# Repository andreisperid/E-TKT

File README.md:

<br>

<a href="https://certification.oshwa.org/br000010.html" target="_blank">
  <picture>
    <source media="(prefers-color-scheme: dark)" srcset="https://user-images.githubusercontent.com/15098003/196943625-ccef0886-9a68-493c-814a-6e63b238b2bd.png">
    <source media="(prefers-color-scheme: light)" srcset="https://user-images.githubusercontent.com/15098003/196943559-973e30a0-acfd-4a96-a7b8-da4f9bf773d8.png">
    
  </picture>
</a>

<br>

<h1 align="center">E-TKT: anachronic label maker</h1>
<h5 align="center">Andrei Speridião - 2022 - <a href="https://andrei.cc">andrei.cc</a></h6>

<br>

<h3 align="center"><i>An open source label maker that fuses together both old and contemporary technology to create something as ubiquitous as... EMBOSSED LABELS!</i></h2>

<br>

By combining simple and widely available embossing tapes in a reliable mechanism with modern connectivity, E-TKT rescues a *would-be future* that did not happen, and at the same time *gets rid of the dependence on proprietary cartridges*, which are environmentally impacting & expensive.

<br>
<br>

<br>

<br><br>

# how does it work?

<picture>
  <source media="(prefers-color-scheme: dark)" srcset="https://user-images.githubusercontent.com/15098003/196457261-b6343e3f-528d-4cbe-a548-1b4f4463e4a1.png">
  <source media="(prefers-color-scheme: light)" srcset="https://user-images.githubusercontent.com/15098003/196947337-6aefe414-159e-483b-9dc4-a49cfc82c548.png">
  
</picture>

An *ESP32* commands the label production and also serves an on demand web application (local) to any device connected in a local network.

***Neither internet is needed, nor installing any app.***

<br>

# documentation 

It's now much more detailed, so I've moved it to a [dedicated page](https://andreisperid.github.io/E-TKT/).

### What you fill find there:

- [🎯 news](https://andreisperid.github.io/E-TKT/news.html): what's going on;
- [🤓 about](https://andreisperid.github.io/E-TKT/about.html): how it started, and why?
- [⚙️ how does it work?](https://andreisperid.github.io/E-TKT/how.html): a more in depth explanation;
- [💡 features](https://andreisperid.github.io/E-TKT/features.html): device and app details;
- [📷 gallery](https://andreisperid.github.io/E-TKT/gallery.html): misc. photos of the device and labeled things;
- [🛠️ do it yourself](https://andreisperid.github.io/E-TKT/diy/diy.html): a **super** detailed guide for you to buy the parts and make your own E-TKT;
- [🧬 iterations](https://andreisperid.github.io/E-TKT/iterations/iterations.html): a log of development so far;
- [⚖️ license](https://andreisperid.github.io/E-TKT/license.html): for firmware, hardware and documentation itself;
- [🏅 credits](https://andreisperid.github.io/E-TKT/credits/credits.html): people that made a difference for the project;
- [📺 media](https://andreisperid.github.io/E-TKT/media.html): where and when it's already been featured.

<br>

### If you ever build one, [I would love to know](mailto:hi@andrei.cc) ;)

### And if you'd like, [donations](https://www.paypal.com/donate/?business=U5QYSBT2TLZL8&no_recurring=0&currency_code=USD) are more than welcome 😍

<br>

### *...for other projects: [andrei.cc](https://andrei.cc)*

<br>

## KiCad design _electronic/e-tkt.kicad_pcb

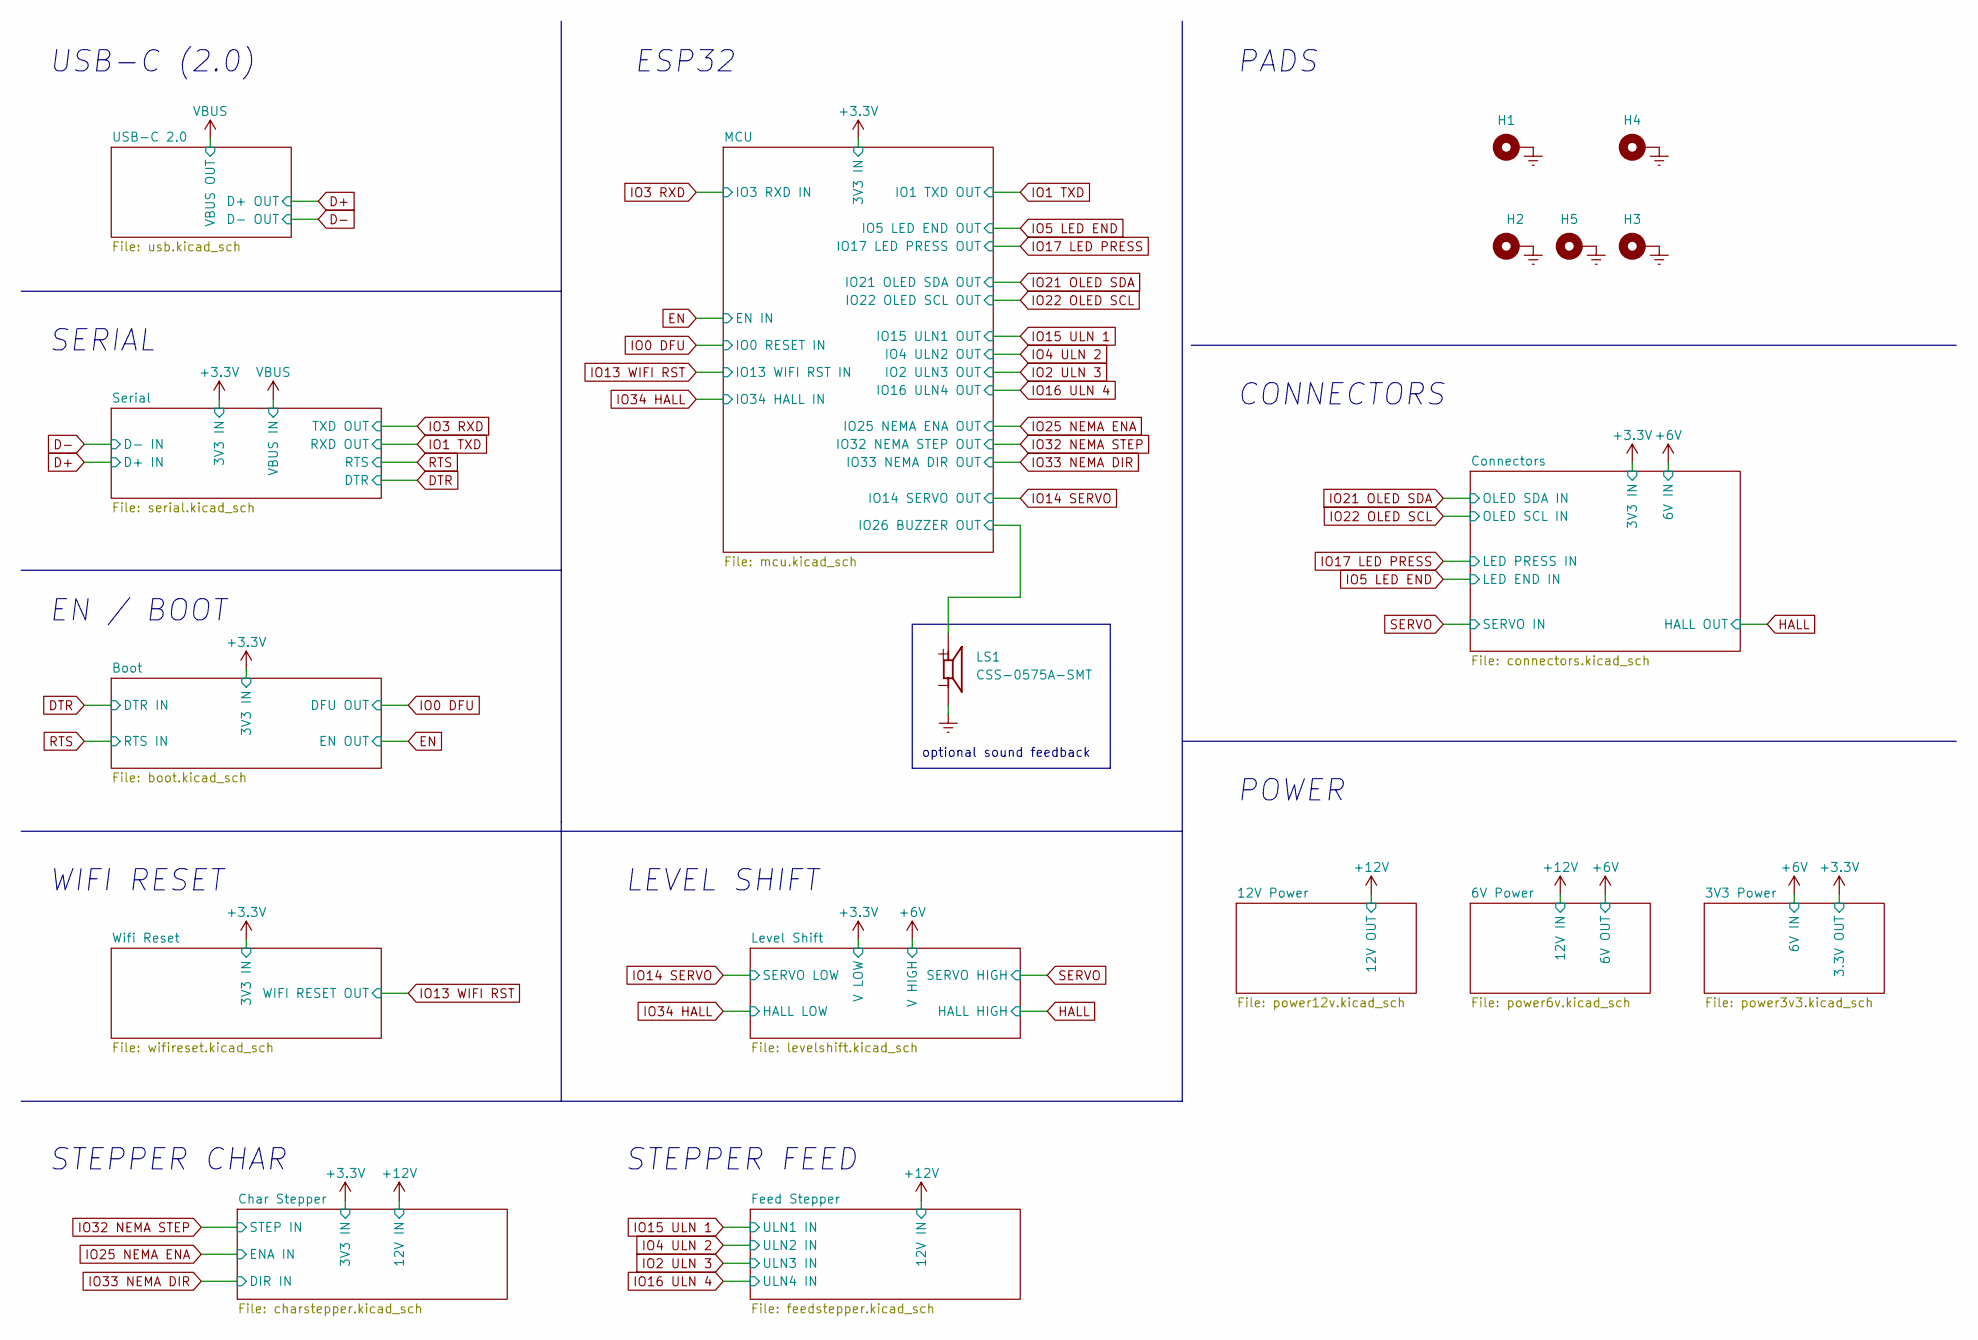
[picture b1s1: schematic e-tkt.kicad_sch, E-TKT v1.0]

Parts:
H1, H2, H3, H4, H5: M3; MountingHole_3.2mm_M3_Pad_Via; Mouser OK
LS1: CSS-0575A-SMT; CUI_CSS-0575A-SMT; Mouser OK

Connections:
/MCU/IO26 BUZZER OUT: LS1.1; also elsewhere on the board

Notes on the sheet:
PADS
POWER
optional sound feedback
SERIAL
EN / BOOT
CONNECTORS
STEPPER CHAR
WIFI RESET
ESP32
LEVEL SHIFT
STEPPER FEED
USB-C (2.0)

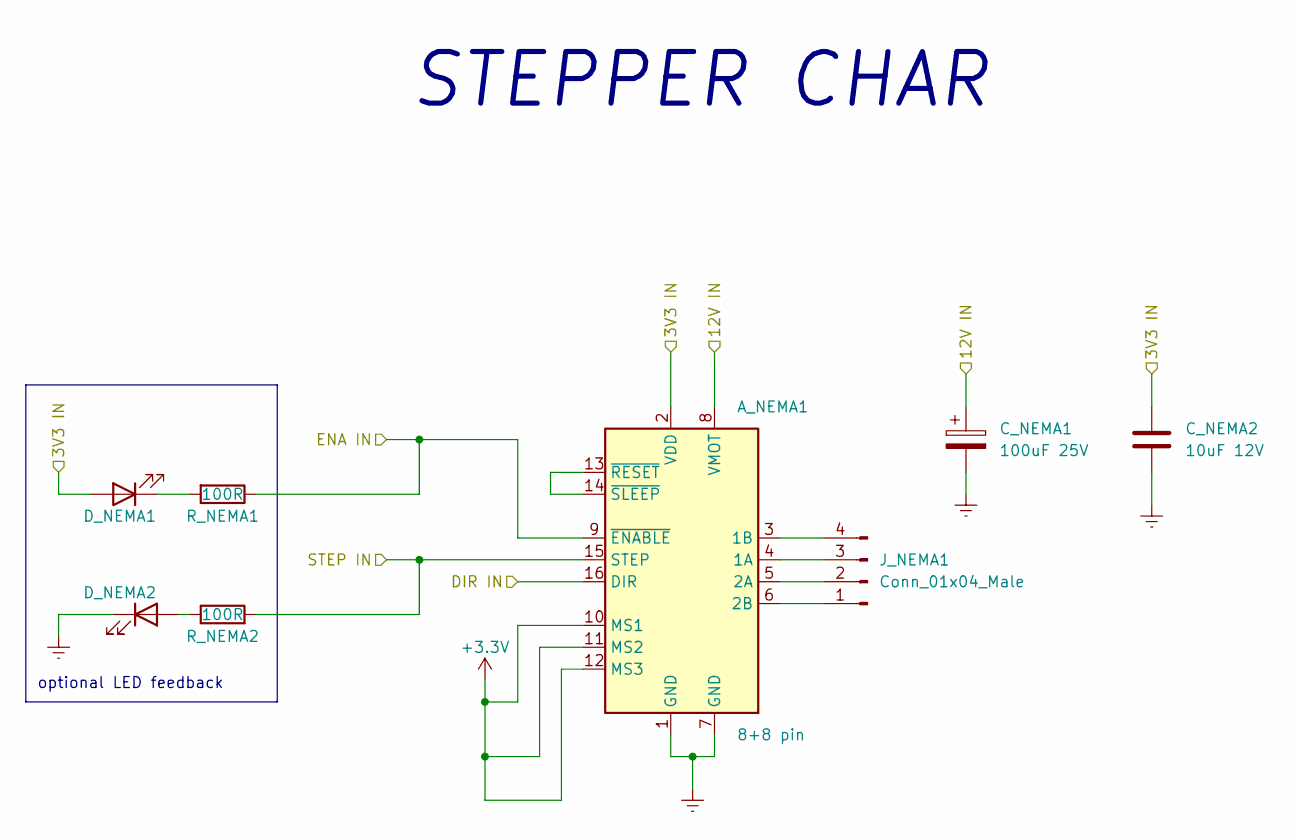
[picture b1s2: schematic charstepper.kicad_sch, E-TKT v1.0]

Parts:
A_NEMA1: 8+8 pin; Pololu_Breakout-16_15.2x20.3mm; Mouser OK
C_NEMA1: 100uF 25V; CP_Elec_6.3x7.7; Mouser OK
C_NEMA2: 10uF 12V; C_0603_1608Metric_Pad1.08x0.95mm_HandSolder; Mouser OK
D_NEMA1, D_NEMA2: LED white; LED_0603_1608Metric_Pad1.05x0.95mm_HandSolder; Mouser OK
J_NEMA1: Conn_01x04_Male; PinHeader_1x04_P2.54mm_Horizontal; Mouser OK
R_NEMA1, R_NEMA2: 100R; R_0603_1608Metric_Pad0.98x0.95mm_HandSolder; Mouser OK

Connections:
+3.3V: A_NEMA1.2 (VDD), A_NEMA1.10 (MS1), A_NEMA1.11 (MS2), A_NEMA1.12 (MS3), C_NEMA2.2, D_NEMA1.2 (A); also elsewhere on the board
+12V: A_NEMA1.8 (VMOT), C_NEMA1.1; also elsewhere on the board
IO25 NEMA ENA: A_NEMA1.9 (~ENABLE), R_NEMA1.1; also elsewhere on the board
IO32 NEMA STEP: A_NEMA1.15 (STEP), R_NEMA2.2; also elsewhere on the board
IO33 NEMA DIR: A_NEMA1.16 (DIR); also elsewhere on the board
unnamed: A_NEMA1.3 (1B), J_NEMA1.4
unnamed: A_NEMA1.4 (1A), J_NEMA1.3
unnamed: A_NEMA1.5 (2A), J_NEMA1.2
unnamed: A_NEMA1.6 (2B), J_NEMA1.1
unnamed: A_NEMA1.13 (~RESET), A_NEMA1.14 (~SLEEP)
unnamed: D_NEMA1.1 (K), R_NEMA1.2
unnamed: D_NEMA2.2 (A), R_NEMA2.1

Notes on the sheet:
optional LED feedback
STEPPER CHAR

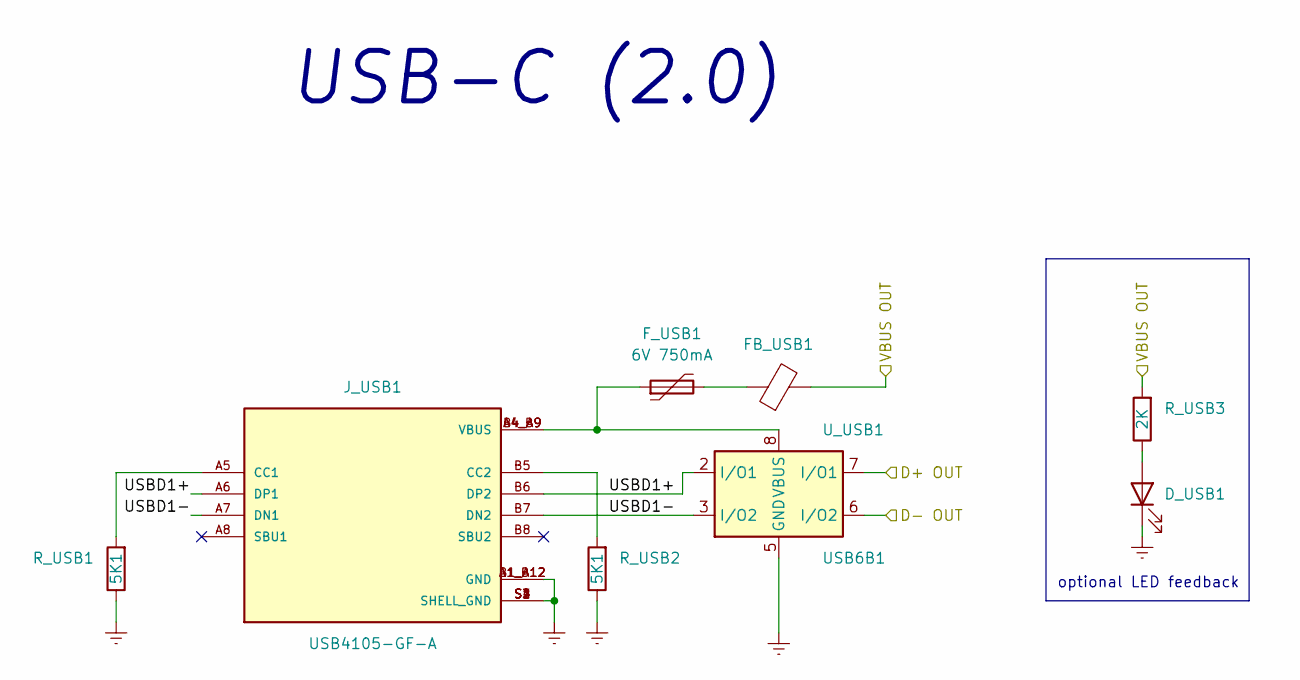
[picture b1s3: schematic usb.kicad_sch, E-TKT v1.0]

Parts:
D_USB1: LED white; LED_0603_1608Metric_Pad1.05x0.95mm_HandSolder; Mouser OK
FB_USB1: 40 Ohms @ 100 MHz 1 Power; L_0805_2012Metric_Pad1.05x1.20mm_HandSolder; Mouser OK
F_USB1: 6V 750mA; Fuse_0805_2012Metric_Pad1.15x1.40mm_HandSolder; Mouser OK
J_USB1: USB4105-GF-A; GCT_USB4105-GF-A; Mouser OK
R_USB1, R_USB2: 5K1; R_0603_1608Metric_Pad0.98x0.95mm_HandSolder; Mouser OK
R_USB3: 2K; R_0603_1608Metric_Pad0.98x0.95mm_HandSolder; Mouser OK
U_USB1: USB6B1; SOIC-8_3.9x4.9mm_P1.27mm; Mouser OK

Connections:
/USB-C 2.0/USBD1+: J_USB1.A6 (DP1), J_USB1.B6 (DP2), U_USB1.2 (I/O1)
/USB-C 2.0/USBD1-: J_USB1.A7 (DN1), J_USB1.B7 (DN2), U_USB1.3 (I/O2)
D+: U_USB1.7 (I/O1); also elsewhere on the board
D-: U_USB1.6 (I/O2); also elsewhere on the board
unnamed: D_USB1.2 (A), R_USB3.1
unnamed: FB_USB1.1, F_USB1.2
unnamed: F_USB1.1, J_USB1.A4_B9 (VBUS), J_USB1.B4_A9 (VBUS), U_USB1.1 (VBUS), U_USB1.8 (VBUS)
unnamed: J_USB1.A5 (CC1), R_USB1.2
unnamed: J_USB1.B5 (CC2), R_USB2.2
VBUS: FB_USB1.2, R_USB3.2; also elsewhere on the board

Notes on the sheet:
USB-C (2.0)
optional LED feedback

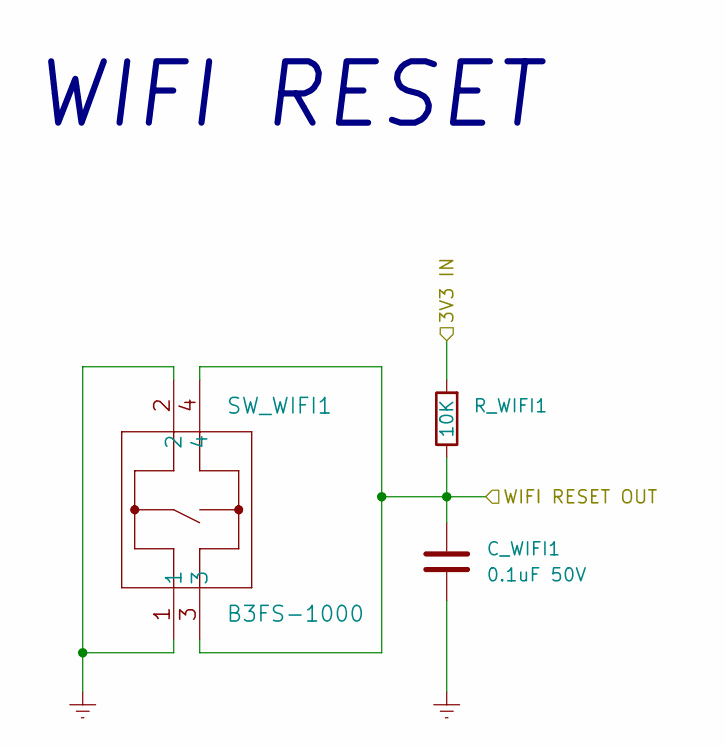
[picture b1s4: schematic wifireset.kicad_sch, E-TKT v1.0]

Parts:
C_WIFI1: 0.1uF 50V; C_0603_1608Metric_Pad1.08x0.95mm_HandSolder; Mouser OK
R_WIFI1: 10K; R_0603_1608Metric_Pad0.98x0.95mm_HandSolder; Mouser OK
SW_WIFI1: B3FS-1000; Mouser OK

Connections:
+3.3V: R_WIFI1.2; also elsewhere on the board
IO13 WIFI RST: C_WIFI1.2, R_WIFI1.1, SW_WIFI1.3, SW_WIFI1.4; also elsewhere on the board

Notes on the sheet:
WIFI RESET

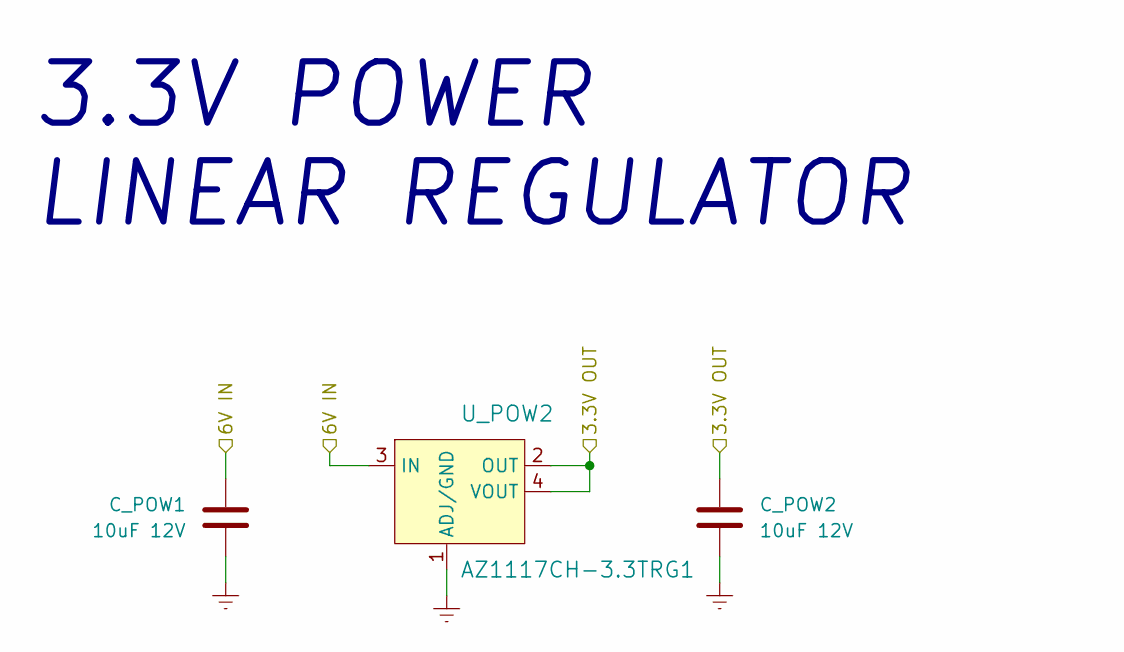
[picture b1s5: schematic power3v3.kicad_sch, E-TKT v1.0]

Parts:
C_POW1, C_POW2: 10uF 12V; C_0603_1608Metric_Pad1.08x0.95mm_HandSolder; Mouser OK
U_POW2: AZ1117CH-3.3TRG1; SOT-223; Mouser OK

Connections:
+3.3V: C_POW2.1, U_POW2.2 (OUT), U_POW2.4 (VOUT); also elsewhere on the board
+6V: C_POW1.1, U_POW2.3 (IN); also elsewhere on the board

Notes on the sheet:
3.3V POWER LINEAR REGULATOR

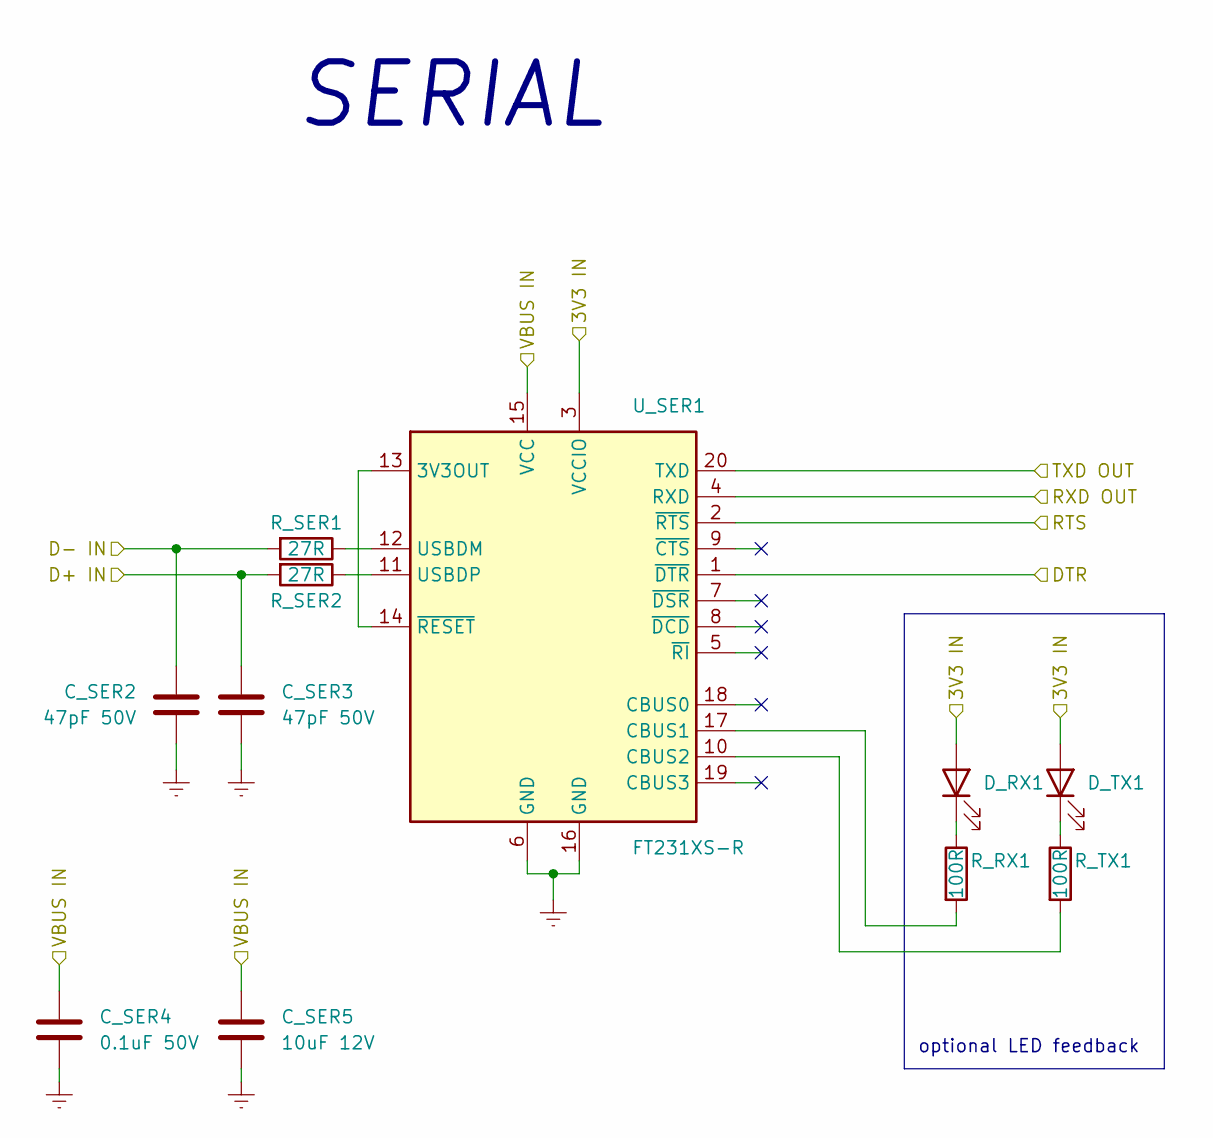
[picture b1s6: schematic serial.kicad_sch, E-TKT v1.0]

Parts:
C_SER2, C_SER3: 47pF 50V; C_0603_1608Metric_Pad1.08x0.95mm_HandSolder; Mouser OK
C_SER4: 0.1uF 50V; C_0603_1608Metric_Pad1.08x0.95mm_HandSolder; Mouser OK
C_SER5: 10uF 12V; C_0603_1608Metric_Pad1.08x0.95mm_HandSolder; Mouser OK
D_RX1: LED white; LED_0603_1608Metric_Pad1.05x0.95mm_HandSolder; Mouser OK
D_TX1: LED white; LED_0603_1608Metric_Pad1.05x0.95mm_HandSolder; Mouser OK
R_RX1: 100R; R_0603_1608Metric_Pad0.98x0.95mm_HandSolder; Mouser OK
R_SER1, R_SER2: 27R; R_0603_1608Metric_Pad0.98x0.95mm_HandSolder; Mouser OK
R_TX1: 100R; R_0603_1608Metric_Pad0.98x0.95mm_HandSolder; Mouser OK
U_SER1: FT231XS-R; SSOP-20_3.9x8.7mm_P0.635mm; Mouser OK

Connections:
+3.3V: D_RX1.2 (A), D_TX1.2 (A), U_SER1.3 (VCCIO); also elsewhere on the board
D+: C_SER3.2, R_SER2.2; also elsewhere on the board
D-: C_SER2.2, R_SER1.2; also elsewhere on the board
DTR: U_SER1.1 (~DTR); also elsewhere on the board
IO1 TXD: U_SER1.4 (RXD); also elsewhere on the board
IO3 RXD: U_SER1.20 (TXD); also elsewhere on the board
unnamed: D_RX1.1 (K), R_RX1.1
unnamed: D_TX1.1 (K), R_TX1.1
unnamed: R_RX1.2, U_SER1.17 (CBUS1)
unnamed: R_SER1.1, U_SER1.12 (USBDM)
unnamed: R_SER2.1, U_SER1.11 (USBDP)
unnamed: R_TX1.2, U_SER1.10 (CBUS2)
unnamed: U_SER1.13 (3V3OUT), U_SER1.14 (~RESET)
RTS: U_SER1.2 (~RTS); also elsewhere on the board
VBUS: C_SER4.1, C_SER5.2, U_SER1.15 (VCC); also elsewhere on the board

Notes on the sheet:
SERIAL
optional LED feedback

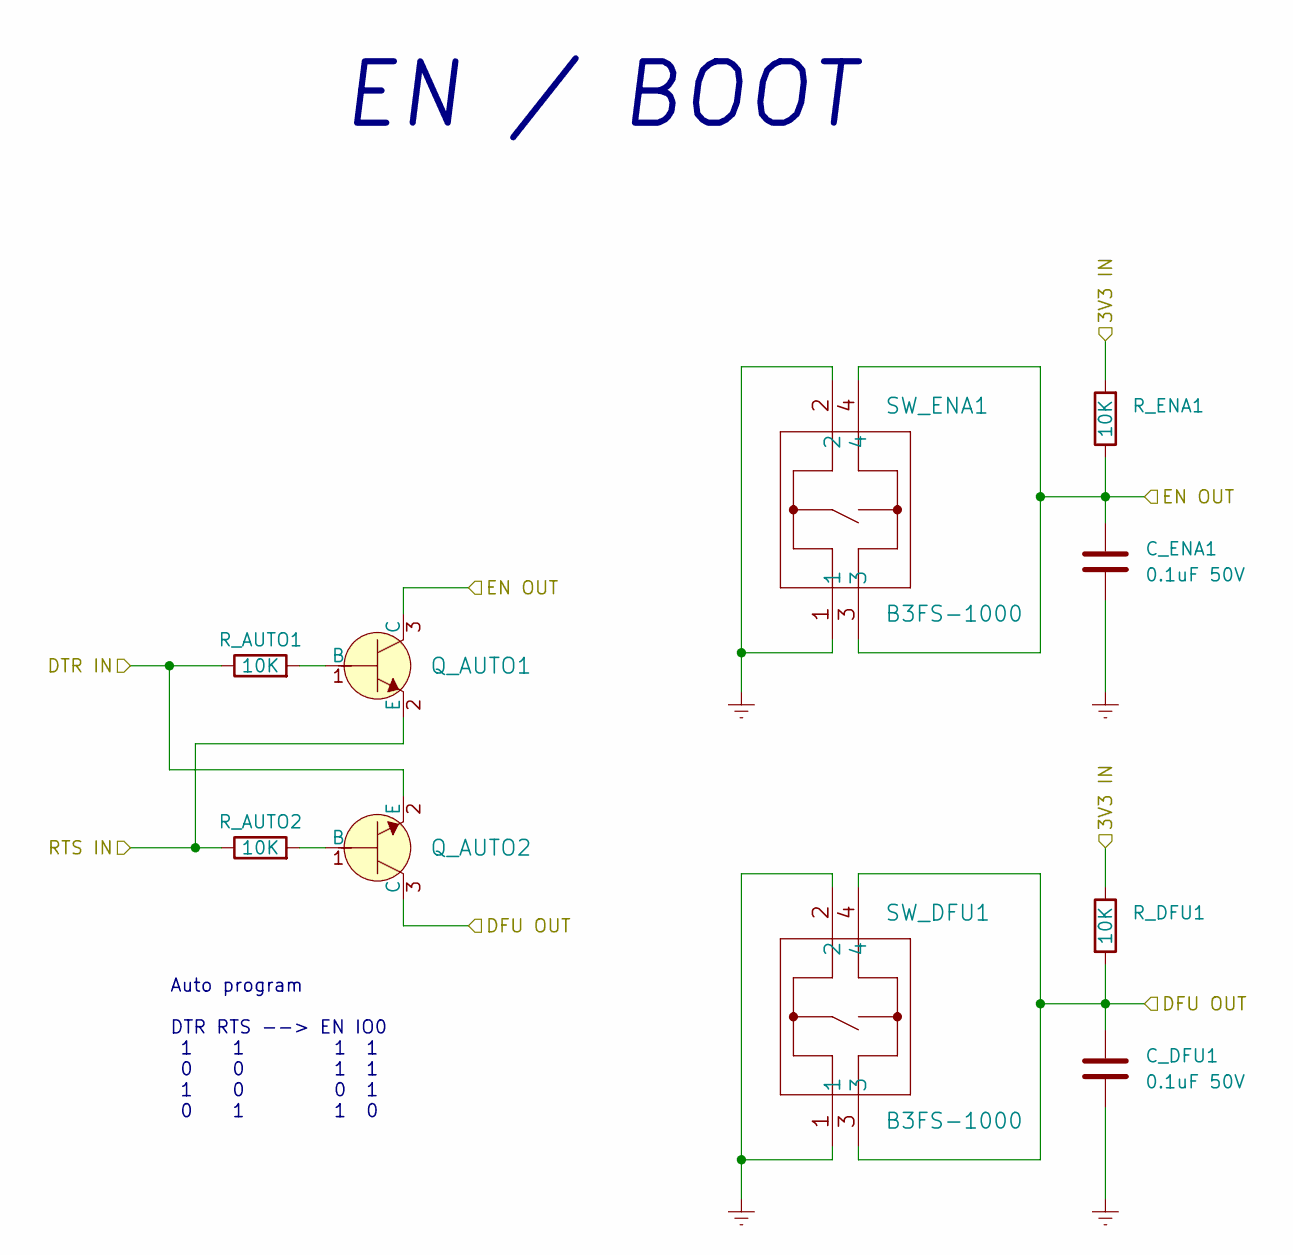
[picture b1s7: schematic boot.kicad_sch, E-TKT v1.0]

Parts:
C_DFU1: 0.1uF 50V; C_0603_1608Metric_Pad1.08x0.95mm_HandSolder; Mouser OK
C_ENA1: 0.1uF 50V; C_0603_1608Metric_Pad1.08x0.95mm_HandSolder; Mouser OK
Q_AUTO1, Q_AUTO2: SS8050; SOT-23_Handsoldering; Mouser OK
R_AUTO1, R_AUTO2: 10K; R_0603_1608Metric_Pad0.98x0.95mm_HandSolder; Mouser OK
R_DFU1: 10K; R_0603_1608Metric_Pad0.98x0.95mm_HandSolder; Mouser OK
R_ENA1: 10K; R_0603_1608Metric_Pad0.98x0.95mm_HandSolder; Mouser OK
SW_DFU1: B3FS-1000; Mouser OK
SW_ENA1: B3FS-1000; Mouser OK

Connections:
+3.3V: R_DFU1.1, R_ENA1.2; also elsewhere on the board
DTR: Q_AUTO2.2 (E), R_AUTO1.1; also elsewhere on the board
EN: C_ENA1.2, Q_AUTO1.3 (C), R_ENA1.1, SW_ENA1.3, SW_ENA1.4; also elsewhere on the board
IO0 DFU: C_DFU1.2, Q_AUTO2.3 (C), R_DFU1.2, SW_DFU1.3, SW_DFU1.4; also elsewhere on the board
unnamed: Q_AUTO1.1 (B), R_AUTO1.2
unnamed: Q_AUTO2.1 (B), R_AUTO2.2
RTS: Q_AUTO1.2 (E), R_AUTO2.1; also elsewhere on the board

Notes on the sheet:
Auto program DTR RTS --> EN IO0 1 1 1 1 0 0 1 1 1 0 0 1 0 1 1 0
EN / BOOT

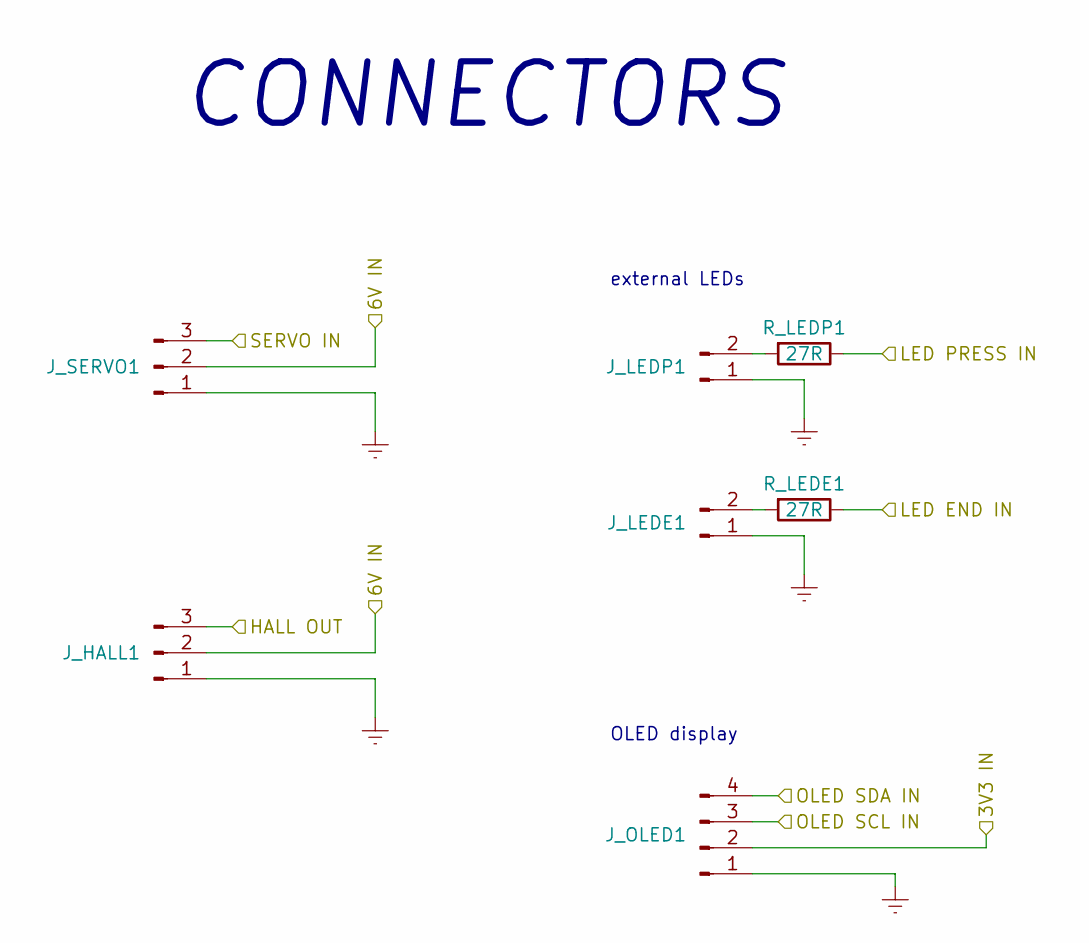
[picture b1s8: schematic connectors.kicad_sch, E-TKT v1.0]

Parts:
J_HALL1: Conn_01x03_Female; PinHeader_1x03_P2.54mm_Vertical; Mouser OK
J_LEDE1: Conn_01x02_Male; PinHeader_1x02_P2.54mm_Vertical; Mouser OK
J_LEDP1: Conn_01x02_Male; PinHeader_1x02_P2.54mm_Vertical; Mouser OK
J_OLED1: Conn_01x04_Male; PinHeader_1x04_P2.54mm_Vertical; Mouser OK
J_SERVO1: Conn_01x03_Male; PinHeader_1x03_P2.54mm_Vertical; Mouser OK
R_LEDE1: 27R; R_0603_1608Metric_Pad0.98x0.95mm_HandSolder; Mouser OK
R_LEDP1: 27R; R_0603_1608Metric_Pad0.98x0.95mm_HandSolder; Mouser OK

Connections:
+3.3V: J_OLED1.2; also elsewhere on the board
+6V: J_HALL1.2, J_SERVO1.2; also elsewhere on the board
HALL: J_HALL1.3; also elsewhere on the board
IO5 LED END: R_LEDE1.1; also elsewhere on the board
IO17 LED PRESS: R_LEDP1.1; also elsewhere on the board
IO21 OLED SDA: J_OLED1.4; also elsewhere on the board
IO22 OLED SCL: J_OLED1.3; also elsewhere on the board
unnamed: J_LEDE1.2, R_LEDE1.2
unnamed: J_LEDP1.2, R_LEDP1.2
SERVO: J_SERVO1.3; also elsewhere on the board

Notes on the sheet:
OLED display
CONNECTORS
external LEDs

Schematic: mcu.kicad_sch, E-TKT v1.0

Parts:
C_MCU1: 0.1uF 50V; C_0603_1608Metric_Pad1.08x0.95mm_HandSolder; Mouser OK
C_MCU2: 10uF 12V; C_0603_1608Metric_Pad1.08x0.95mm_HandSolder; Mouser OK
U_MCU1: ESP32-WROOM-32; Mouser OK

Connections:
+3.3V: C_MCU1.1, C_MCU2.2, U_MCU1.2 (VDD); also elsewhere on the board
/MCU/IO26 BUZZER OUT: U_MCU1.11 (IO26); also elsewhere on the board
EN: U_MCU1.3 (EN); also elsewhere on the board
IO0 DFU: U_MCU1.25 (IO0); also elsewhere on the board
IO1 TXD: U_MCU1.35 (TXD0/IO1); also elsewhere on the board
IO2 ULN 3: U_MCU1.24 (IO2); also elsewhere on the board
IO3 RXD: U_MCU1.34 (RXD0/IO3); also elsewhere on the board
IO4 ULN 2: U_MCU1.26 (IO4); also elsewhere on the board
IO5 LED END: U_MCU1.29 (IO5); also elsewhere on the board
IO13 WIFI RST: U_MCU1.16 (IO13); also elsewhere on the board
IO14 SERVO: U_MCU1.13 (IO14); also elsewhere on the board
IO15 ULN 1: U_MCU1.23 (IO15); also elsewhere on the board
IO16 ULN 4: U_MCU1.27 (IO16); also elsewhere on the board
IO17 LED PRESS: U_MCU1.28 (IO17); also elsewhere on the board
IO21 OLED SDA: U_MCU1.33 (IO21); also elsewhere on the board
IO22 OLED SCL: U_MCU1.36 (IO22); also elsewhere on the board
IO25 NEMA ENA: U_MCU1.10 (IO25); also elsewhere on the board
IO32 NEMA STEP: U_MCU1.8 (IO32); also elsewhere on the board
IO33 NEMA DIR: U_MCU1.9 (IO33); also elsewhere on the board
IO34 HALL: U_MCU1.6 (IO34); also elsewhere on the board

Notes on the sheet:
ESP32

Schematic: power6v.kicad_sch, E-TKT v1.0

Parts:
C_ALT6V_1: 0.33uF 50V; C_0603_1608Metric_Pad1.08x0.95mm_HandSolder; Mouser OK
C_ALT6V_2: 0.1uF 50V; C_0603_1608Metric_Pad1.08x0.95mm_HandSolder; Mouser OK
C_POW_6V_FF1: 47pF 50V; C_0603_1608Metric_Pad1.08x0.95mm_HandSolder; Mouser OK
C_POW_BST1: 0.1uF 50V; C_0603_1608Metric_Pad1.08x0.95mm_HandSolder; Mouser OK
C_POW_IN1, C_POW_IN2, C_POW_IN3: 22uF 25V; C_1210_3225Metric_Pad1.33x2.70mm_HandSolder; Mouser OK
C_POW_OUT1, C_POW_OUT2, C_POW_OUT3, C_POW_OUT4, C_POW_OUT5: 22uF 25V; C_1210_3225Metric_Pad1.33x2.70mm_HandSolder; Mouser OK
J_6v_ALT6V1, J_12v_ALT6V1: TestPoint; TestPoint_Pad_D1.5mm; Mouser OK
J_GND_ALT6V1: TestPoint; TestPoint_Pad_D1.5mm; Mouser OK
L1: SRP6060FA-100M; SRP6060FA-4R7M; Mouser OK
R_POW_FBT1: 100K; R_0603_1608Metric_Pad0.98x0.95mm_HandSolder; Mouser OK
R_POW_FFB1: 11K; R_0603_1608Metric_Pad0.98x0.95mm_HandSolder; Mouser OK
U_POW1: SOT-23-6_Handsoldering; Mouser N

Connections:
+6V: C_ALT6V_2.1, C_POW_6V_FF1.1, C_POW_OUT1.1, C_POW_OUT2.1, C_POW_OUT3.1, C_POW_OUT4.1, C_POW_OUT5.1, J_6v_ALT6V1.1, L1.2, R_POW_FBT1.2; also elsewhere on the board
+12V: C_ALT6V_1.2, C_POW_IN1.1, C_POW_IN2.1, C_POW_IN3.1, J_12v_ALT6V1.1, U_POW1.3 (VIN); also elsewhere on the board
unnamed: C_POW_6V_FF1.2, R_POW_FBT1.1, R_POW_FFB1.2, U_POW1.4 (FB)
unnamed: C_POW_BST1.1, U_POW1.6 (BOOT)
unnamed: C_POW_BST1.2, L1.1, U_POW1.2 (SW)

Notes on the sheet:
alternative 6V output: 7806 linear regulator
6V POWER BUCK CONVERTER

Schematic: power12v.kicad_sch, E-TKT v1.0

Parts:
D_POW2: LED white; LED_0603_1608Metric_Pad1.05x0.95mm_HandSolder; Mouser OK
J_POW1: Barrel_Jack_Switch; BarrelJack_GCT_DCJ200-10-A_Horizontal; Mouser OK
R_POW6: 5K1; R_0603_1608Metric_Pad0.98x0.95mm_HandSolder; Mouser OK

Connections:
+12V: J_POW1.1, R_POW6.1; also elsewhere on the board
unnamed: D_POW2.2 (A), R_POW6.2

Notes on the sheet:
optional LED feedback
12V POWER + LATCH SWITCH

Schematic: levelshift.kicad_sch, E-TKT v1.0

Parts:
D_HALL1: LED white; LED_0603_1608Metric_Pad1.05x0.95mm_HandSolder; Mouser OK
D_SERVO1: LED white; LED_0603_1608Metric_Pad1.05x0.95mm_HandSolder; Mouser OK
Q_HALL1: BSS138LT3G; SOT-23_Handsoldering; Mouser OK
Q_SERVO1: BSS138LT3G; SOT-23_Handsoldering; Mouser OK
R_HALL1, R_HALL2: 10K; R_0603_1608Metric_Pad0.98x0.95mm_HandSolder; Mouser OK
R_HALL3: 100R; R_0603_1608Metric_Pad0.98x0.95mm_HandSolder; Mouser OK
R_SERVO1, R_SERVO2: 10K; R_0603_1608Metric_Pad0.98x0.95mm_HandSolder; Mouser OK
R_SERVO3: 100R; R_0603_1608Metric_Pad0.98x0.95mm_HandSolder; Mouser OK

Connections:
+3.3V: D_HALL1.2 (A), D_SERVO1.2 (A), Q_HALL1.1 (G), Q_SERVO1.1 (G), R_HALL2.2, R_SERVO2.2; also elsewhere on the board
+6V: R_HALL1.2, R_SERVO1.2; also elsewhere on the board
HALL: Q_HALL1.3 (D), R_HALL1.1; also elsewhere on the board
IO14 SERVO: Q_SERVO1.2 (S), R_SERVO2.1, R_SERVO3.1; also elsewhere on the board
IO34 HALL: Q_HALL1.2 (S), R_HALL2.1, R_HALL3.1; also elsewhere on the board
unnamed: D_HALL1.1 (K), R_HALL3.2
unnamed: D_SERVO1.1 (K), R_SERVO3.2
SERVO: Q_SERVO1.3 (D), R_SERVO1.1; also elsewhere on the board

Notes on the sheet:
optional LED feedback
LEVEL SHIFT

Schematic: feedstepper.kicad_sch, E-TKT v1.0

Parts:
C_STP1: 10uF 12V; C_0603_1608Metric_Pad1.08x0.95mm_HandSolder; Mouser OK
D_STP1, D_STP2, D_STP3, D_STP4: LED white; LED_0603_1608Metric_Pad1.05x0.95mm_HandSolder; Mouser OK
J_28byj-48-12v_1: Conn_01x05_Male; PinHeader_1x05_P2.54mm_Vertical; Mouser OK
R_STP1, R_STP2, R_STP3, R_STP4: 5K1; R_0603_1608Metric_Pad0.98x0.95mm_HandSolder; Mouser OK
U_STP1: ULN2003; SOIC-16_3.9x9.9mm_P1.27mm; Mouser OK

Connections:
+12V: C_STP1.2, J_28byj-48-12v_1.1, R_STP1.1, R_STP2.1, R_STP3.1, R_STP4.1, U_STP1.9 (COM); also elsewhere on the board
IO2 ULN 3: U_STP1.3 (I3); also elsewhere on the board
IO4 ULN 2: U_STP1.2 (I2); also elsewhere on the board
IO15 ULN 1: U_STP1.1 (I1); also elsewhere on the board
IO16 ULN 4: U_STP1.4 (I4); also elsewhere on the board
unnamed: D_STP1.1 (K), J_28byj-48-12v_1.2, U_STP1.16 (O1)
unnamed: D_STP1.2 (A), R_STP1.2
unnamed: D_STP2.1 (K), J_28byj-48-12v_1.3, U_STP1.15 (O2)
unnamed: D_STP2.2 (A), R_STP2.2
unnamed: D_STP3.1 (K), J_28byj-48-12v_1.4, U_STP1.14 (O3)
unnamed: D_STP3.2 (A), R_STP3.2
unnamed: D_STP4.1 (K), J_28byj-48-12v_1.5, U_STP1.13 (O4)
unnamed: D_STP4.2 (A), R_STP4.2

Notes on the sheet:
optional LED feedback
STEPPER FEED

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
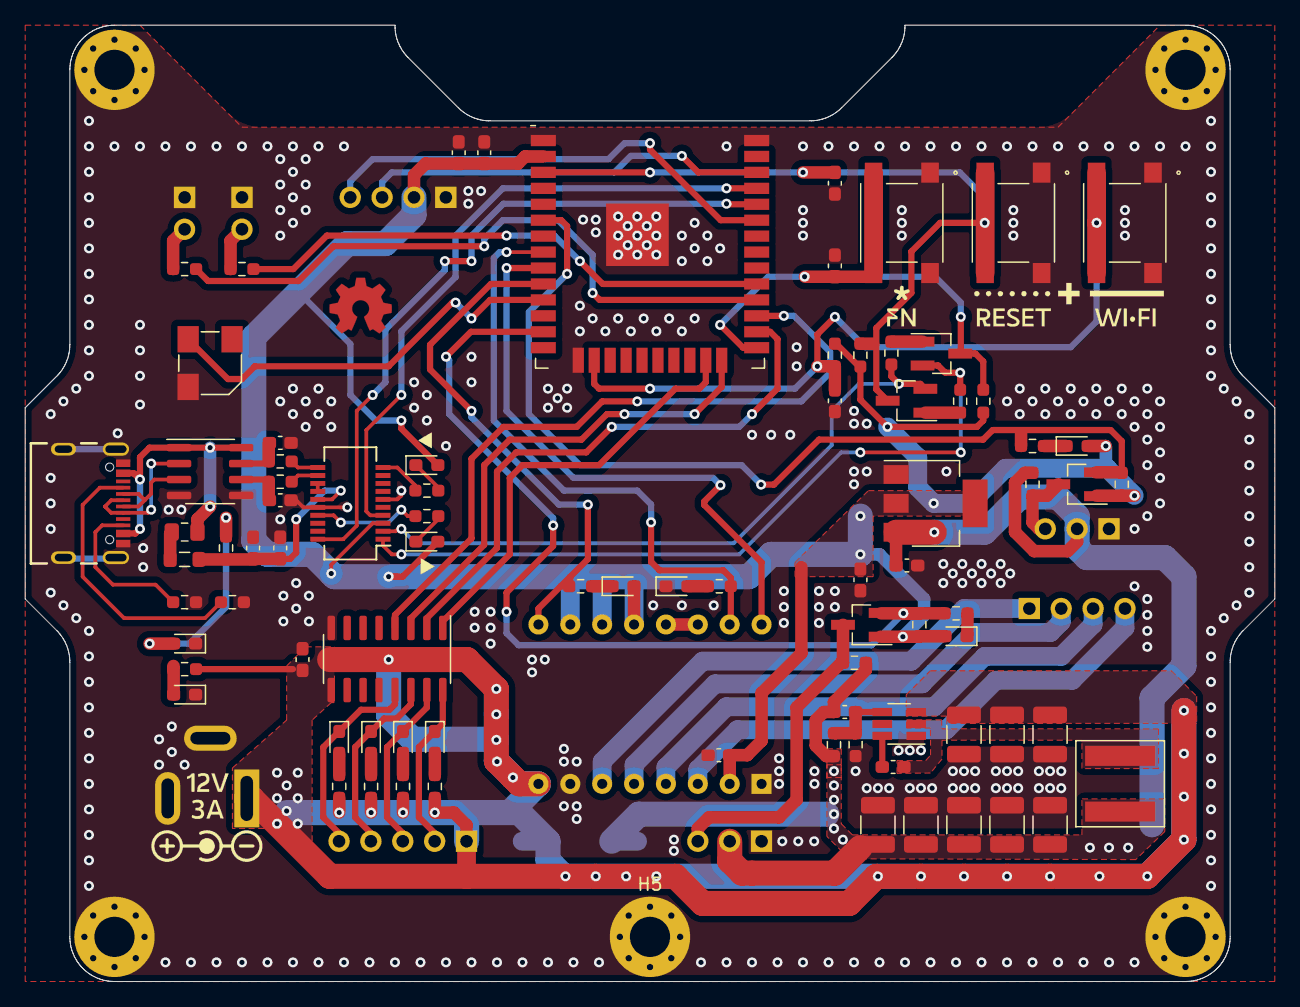
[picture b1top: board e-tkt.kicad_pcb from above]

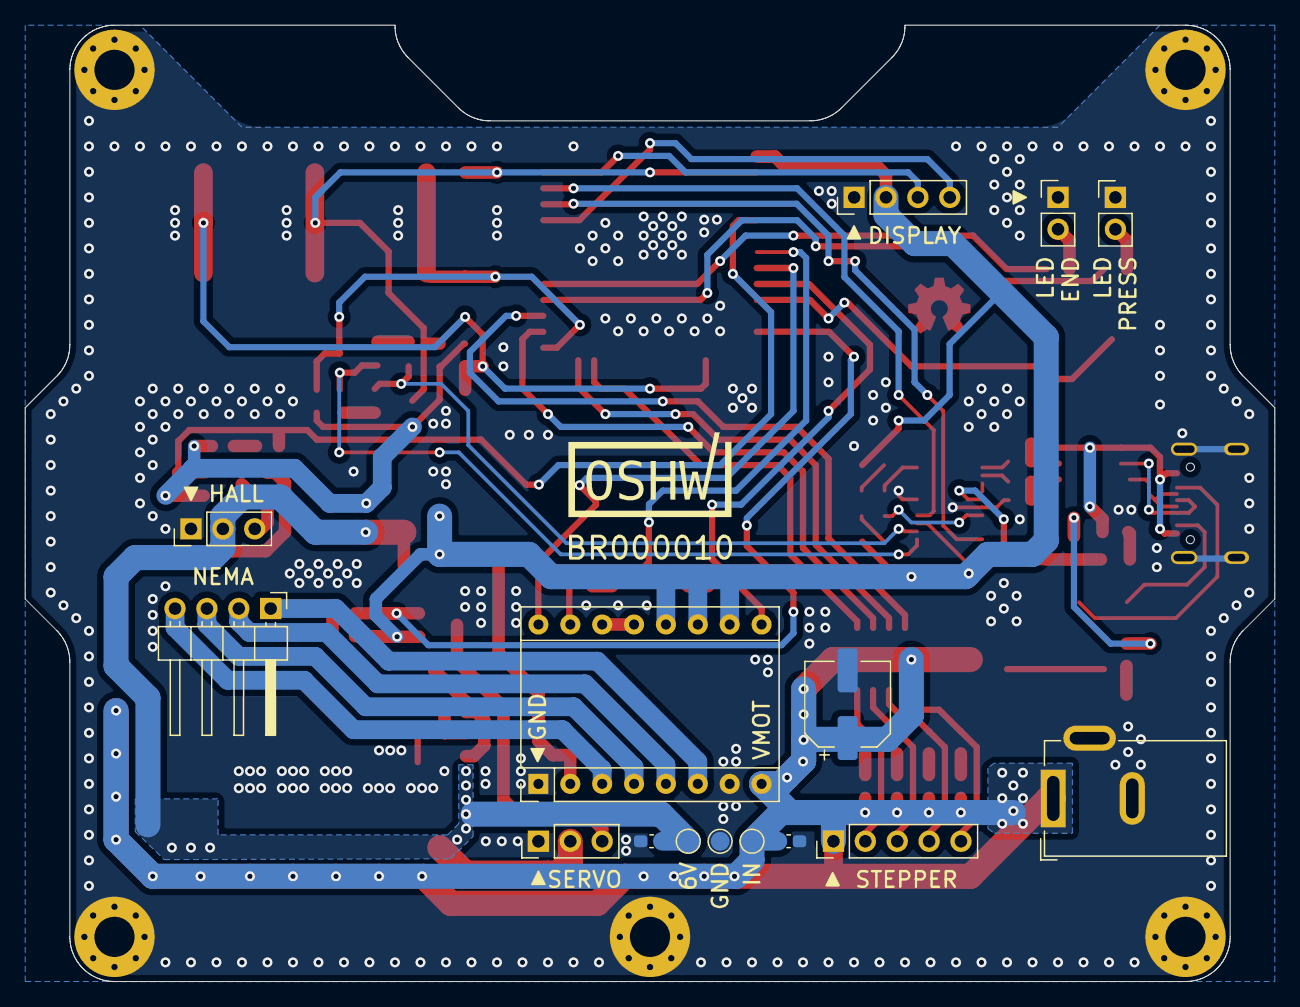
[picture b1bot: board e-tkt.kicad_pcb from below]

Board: 4 copper layers, 99.6 x 76.2 mm, 102 parts (15 on the bottom side), 69 nets.

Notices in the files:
parts and their libraries:
Copyright 2021 Accelerated Designs. All rights reserved.
